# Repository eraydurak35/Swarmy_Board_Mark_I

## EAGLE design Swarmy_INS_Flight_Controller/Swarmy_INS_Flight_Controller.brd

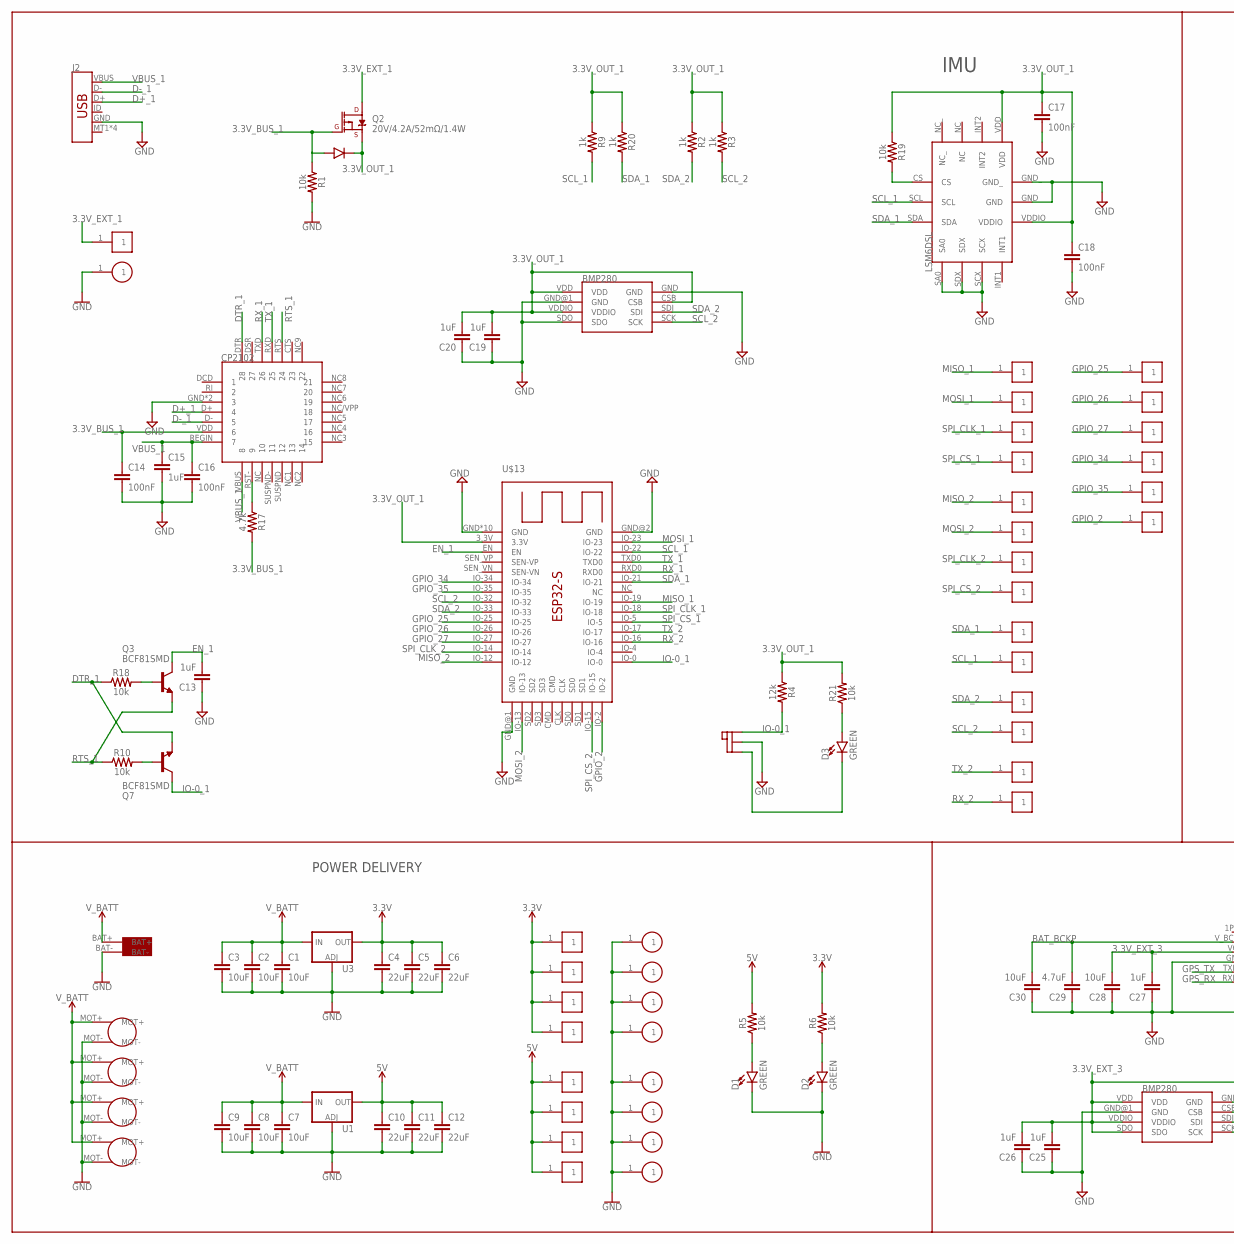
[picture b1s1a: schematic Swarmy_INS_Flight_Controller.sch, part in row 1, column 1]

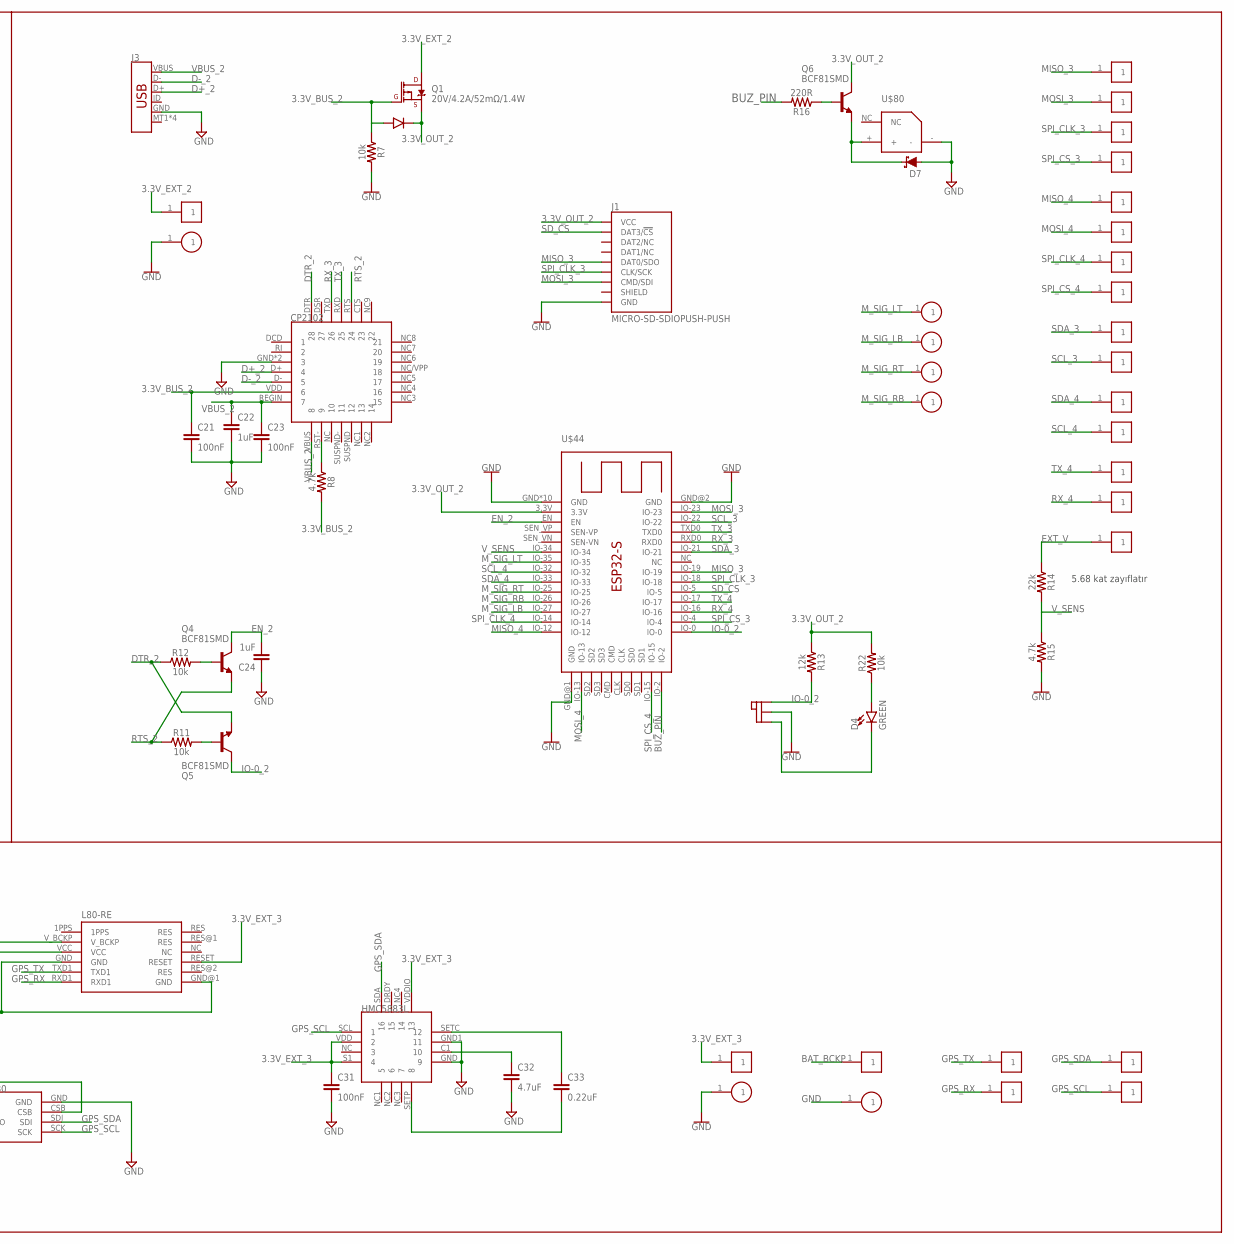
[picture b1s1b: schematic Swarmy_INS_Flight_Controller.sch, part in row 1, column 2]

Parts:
C1, C2, C3, C7, C8, C9, C28, C30: 10uF; 0603
C4, C5, C6, C10, C11, C12: 22uF; 0603
C13, C15, C19, C20, C22, C24, C25, C26, C27: 1uF; 0603
C14, C16, C17, C18, C21, C23, C31: 100nF; 0603
C29, C32: 4.7uF; 0603
C33: 0.22uF; 0603
D1, D2, D3, D4: GREEN; LED-0603
D7: 120mA/40V/370mV; SOD-523
J1: MICRO-SD-SDIOPUSH-PUSH; MICRO-SD-SOCKET
J2, J3: USB_MICRO-B_SMT; USB-MICROB
Q1, Q2: 20V/4.2A/52mΩ/1.4W; SOT23-3
Q3, Q4, Q5, Q6, Q7: BCF81SMD; SOT23-BEC
R1, R5, R6, R7, R10, R11, R12, R18, R19, R21, R22: 10k; 0603
R2, R3, R9, R20: 1k; 0603
R4, R13: 12k; 0603
R8, R15, R17: 4.7k; 0603
R14: 22k; 0603
R16: 220R; 0603
U1, U3: V_REG_LM1117SOT223; SOT223
U$1: 6X5MM_BATTERY_SOLDER_PADS
U$2, U$3, U$4, U$5: 3X4.5MM_MOTOR_SOLDER_PADS
U$6, U$7, U$8, U$9, U$10, U$11, U$12, U$22, U$23, U$29, U$30, U$31, U$32, U$33, U$34, U$35, U$36, U$37, U$38, U$39, U$40, U$41, U$42, U$45, U$50, U$51, U$52, U$53, U$54, U$55, U$56, U$57, U$58, U$59, U$60, U$61, U$62, U$63, U$65, U$67, U$69, U$71, U$72, U$73, U$74, U$81, U$82, U$83, U$84, U$85, U$86: 2X2MM_SQUARE_PAD
U$13, U$44: ESP32-S
U$14, U$15, U$16, U$17, U$18, U$19, U$20, U$21, U$24, U$46, U$68, U$70: 2X2MM_PAD
U$25, U$47: SOD_123_DIODE; SOD_23_DIODE
U$26: LSM6DSL_6DOF
U$27, U$66: BMP280
U$28, U$48: CP2102_SERIAL_TTL
U$43, U$49: SMD_SLIDE_SWITCH
U$64: L80-RE-M37
U$75: HMC5883L
U$76, U$77, U$78, U$79: 2X2MM_ROUND_PAD
U$80: PASIVE_BUZZER_5MM_X_5MM_20MM

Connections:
3.3V: C4.1, C5.1, C6.1, R6.2, U3.2 (OUT), U3.4 (OUT), U$6.1, U$7.1, U$8.1, U$22.1
3.3V_BUS_1: C14.1, Q2.1 (G), R1.1, R17.2, U$25.A, U$28.VDD (6)
3.3V_BUS_2: C21.1, Q1.1 (G), R7.1, R8.2, U$47.A, U$48.VDD (6)
3.3V_EXT_1: Q2.3 (D), U$23.1
3.3V_EXT_2: Q1.3 (D), U$45.1
3.3V_EXT_3: C25.2, C26.2, C27.2, C28.2, C31.1, U$64.RESET, U$64.VCC, U$66.CSB, U$66.SDO, U$66.VDD, U$66.VDDIO, U$67.1, U$75.S1 (4), U$75.VDD (2), U$75.VDDIO (13)
3.3V_OUT_1: C17.1, C18.1, C19.2, C20.2, Q2.2 (S), R2.1, R3.1, R4.1, R9.1, R19.1, R20.1, R21.2, U$13.3.3V, U$25.K, U$26.VDD, U$26.VDDIO, U$27.CSB, U$27.VDD, U$27.VDDIO
3.3V_OUT_2: J1.VCC, Q1.2 (S), Q6.C, R13.1, R22.2, U$44.3.3V, U$47.K
5V: C10.1, C11.1, C12.1, R5.2, U1.2 (OUT), U1.4 (OUT), U$9.1, U$10.1, U$11.1, U$12.1
BAT_BCKP: C29.2, C30.2, U$64.V_BCKP, U$69.1
BUZ_PIN: R16.2, U$44.IO-2
D+_1: J2.D+, U$28.D+ (4)
D+_2: J3.D+, U$48.D+ (4)
D-_1: J2.D-, U$28.D- (5)
D-_2: J3.D-, U$48.D- (5)
DTR_1: Q7.E, R18.1, U$28.DTR (28)
DTR_2: Q5.E, R12.1, U$48.DTR (28)
EN_1: C13.2, Q3.C, U$13.EN
EN_2: C24.2, Q4.C, U$44.EN
EXT_V: R14.1, U$65.1
GND: C1.2, C2.2, C3.2, C4.2, C5.2, C6.2, C7.2, C8.2, C9.2, C10.2, C11.2, C12.2, C13.1, C14.2, C15.2, C16.2, C17.2, C18.2, C19.1, C20.1, C21.2, C22.2, C23.2, C24.1, C25.1, C26.1, C27.1, C28.1, C29.1, C30.1, C31.2, C32.2, D1.C, D2.C, D7.A, J1.GND, J1.GND1 (GND), J1.GND3 (GND), J2.GND, J3.GND, R1.2, R7.2, R15.2, U1.1 (ADJ), U3.1 (ADJ), U$1.BAT-, U$2.MOT-, U$3.MOT-, U$4.MOT-, U$5.MOT-, U$13.GND, U$13.GND@1 (GND), U$13.GND@2 (GND), U$13.GND@3 (GND), U$13.GND@4 (GND), U$13.GND@5 (GND), U$13.GND@6 (GND), U$13.GND@7 (GND), U$13.GND@8 (GND), U$13.GND@9 (GND), U$13.GND@10 (GND), U$13.GND@11 (GND), U$14.1, U$15.1, U$16.1, U$17.1, U$18.1, U$19.1, U$20.1, U$21.1, U$24.1, U$26.GND, U$26.GND_, U$26.SA0, U$26.SCX, U$26.SDX, U$27.GND, U$27.GND@1 (GND), U$27.SDO, U$28.GND (3), U$28.GND1 (3), U$43.2, U$44.GND, U$44.GND@1 (GND), U$44.GND@2 (GND), U$44.GND@3 (GND), U$44.GND@4 (GND), U$44.GND@5 (GND), U$44.GND@6 (GND), U$44.GND@7 (GND), U$44.GND@8 (GND), U$44.GND@9 (GND), U$44.GND@10 (GND), U$44.GND@11 (GND), U$46.1, U$48.GND (3), U$48.GND1 (3), U$49.2, U$64.GND, U$64.GND@1 (GND), U$66.GND, U$66.GND@1 (GND), U$68.1, U$70.1, U$75.GND (9), U$75.GND1 (11), U$80.-
GPIO_2: U$13.IO-2, U$86.1
GPIO_25: U$13.IO-25, U$81.1
GPIO_26: U$13.IO-26, U$82.1
GPIO_27: U$13.IO-27, U$83.1
GPIO_34: U$13.IO-34, U$84.1
GPIO_35: U$13.IO-35, U$85.1
GPS_RX: U$64.RXD1, U$72.1
GPS_SCL: U$66.SCK, U$74.1, U$75.SCL (1)
GPS_SDA: U$66.SDI, U$73.1, U$75.SDA (16)
GPS_TX: U$64.TXD1, U$71.1
IO-0_1: Q7.C, R4.2, U$13.IO-0, U$43.3
IO-0_2: Q5.C, R13.2, U$44.IO-0, U$49.3
MISO_1: U$13.IO-19, U$29.1
MISO_2: U$13.IO-12, U$33.1
MISO_3: J1.DO/DAT0 (DAT0/SDO), U$44.IO-19, U$50.1
MISO_4: U$44.IO-12, U$54.1
MOSI_1: U$13.IO-23, U$30.1
MOSI_2: U$13.IO-13, U$34.1
MOSI_3: J1.DI/CMD (CMD/SDI), U$44.IO-23, U$51.1
MOSI_4: U$44.IO-13, U$55.1
M_SIG_LB: U$44.IO-27, U$77.1
M_SIG_LT: U$44.IO-35, U$76.1
M_SIG_RB: U$44.IO-26, U$79.1
M_SIG_RT: U$44.IO-25, U$78.1
unnamed: D1.A, R5.1
unnamed: D2.A, R6.1
unnamed: R8.1, U$48.RST- (9)
unnamed: Q5.B, R11.2
unnamed: Q4.B, R12.2
unnamed: D3.A, R21.1
unnamed: D4.A, R22.1
unnamed: D3.C, U$43.1
unnamed: D4.C, U$49.1
unnamed: Q6.B, R16.1
unnamed: R17.1, U$28.RST- (9)
unnamed: D7.C, Q6.E, U$80.+
unnamed: Q3.B, R18.2
unnamed: R19.2, U$26.CS
unnamed: Q7.B, R10.2
unnamed: C33.2, U$75.SETP (8)
unnamed: C32.1, U$75.C1 (10)
unnamed: C33.1, U$75.SETC (12)
RTS_1: Q3.E, R10.1, U$28.RTS (24)
RTS_2: Q4.E, R11.1, U$48.RTS (24)
RX_1: U$13.RXD0, U$28.TXD (26)
RX_2: U$13.IO-16, U$42.1
RX_3: U$44.RXD0, U$48.TXD (26)
RX_4: U$44.IO-16, U$63.1
SCL_1: R9.2, U$13.IO-22, U$26.SCL, U$38.1
SCL_2: R3.2, U$13.IO-32, U$27.SCK, U$40.1
SCL_3: U$44.IO-22, U$59.1
SCL_4: U$44.IO-32, U$61.1
SDA_1: R20.2, U$13.IO-21, U$26.SDA, U$37.1
SDA_2: R2.2, U$13.IO-33, U$27.SDI, U$39.1
SDA_3: U$44.IO-21, U$58.1
SDA_4: U$44.IO-33, U$60.1
SD_CS: J1.CS/DAT3 (DAT3/!CS!), U$44.IO-5
SPI_CLK_1: U$13.IO-18, U$31.1
SPI_CLK_2: U$13.IO-14, U$35.1
SPI_CLK_3: J1.SCLK (CLK/SCK), U$44.IO-18, U$52.1
SPI_CLK_4: U$44.IO-14, U$56.1
SPI_CS_1: U$13.IO-5, U$32.1
SPI_CS_2: U$13.IO-15, U$36.1
SPI_CS_3: U$44.IO-4, U$53.1
SPI_CS_4: U$44.IO-15, U$57.1
TX_1: U$13.TXD0, U$28.RXD (25)
TX_2: U$13.IO-17, U$41.1
TX_3: U$44.TXD0, U$48.RXD (25)
TX_4: U$44.IO-17, U$62.1
VBUS_1: C15.1, C16.1, J2.VBUS, U$28.REGIN (7), U$28.VBUS (8)
VBUS_2: C22.1, C23.1, J3.VBUS, U$48.REGIN (7), U$48.VBUS (8)
V_BATT: C1.1, C2.1, C3.1, C7.1, C8.1, C9.1, U1.3 (IN), U3.3 (IN), U$1.BAT+, U$2.MOT+, U$3.MOT+, U$4.MOT+, U$5.MOT+
V_SENS: R14.2, R15.1, U$44.IO-34

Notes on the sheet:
POWER DELIVERY
IMU
5.68 kat zayıflatır

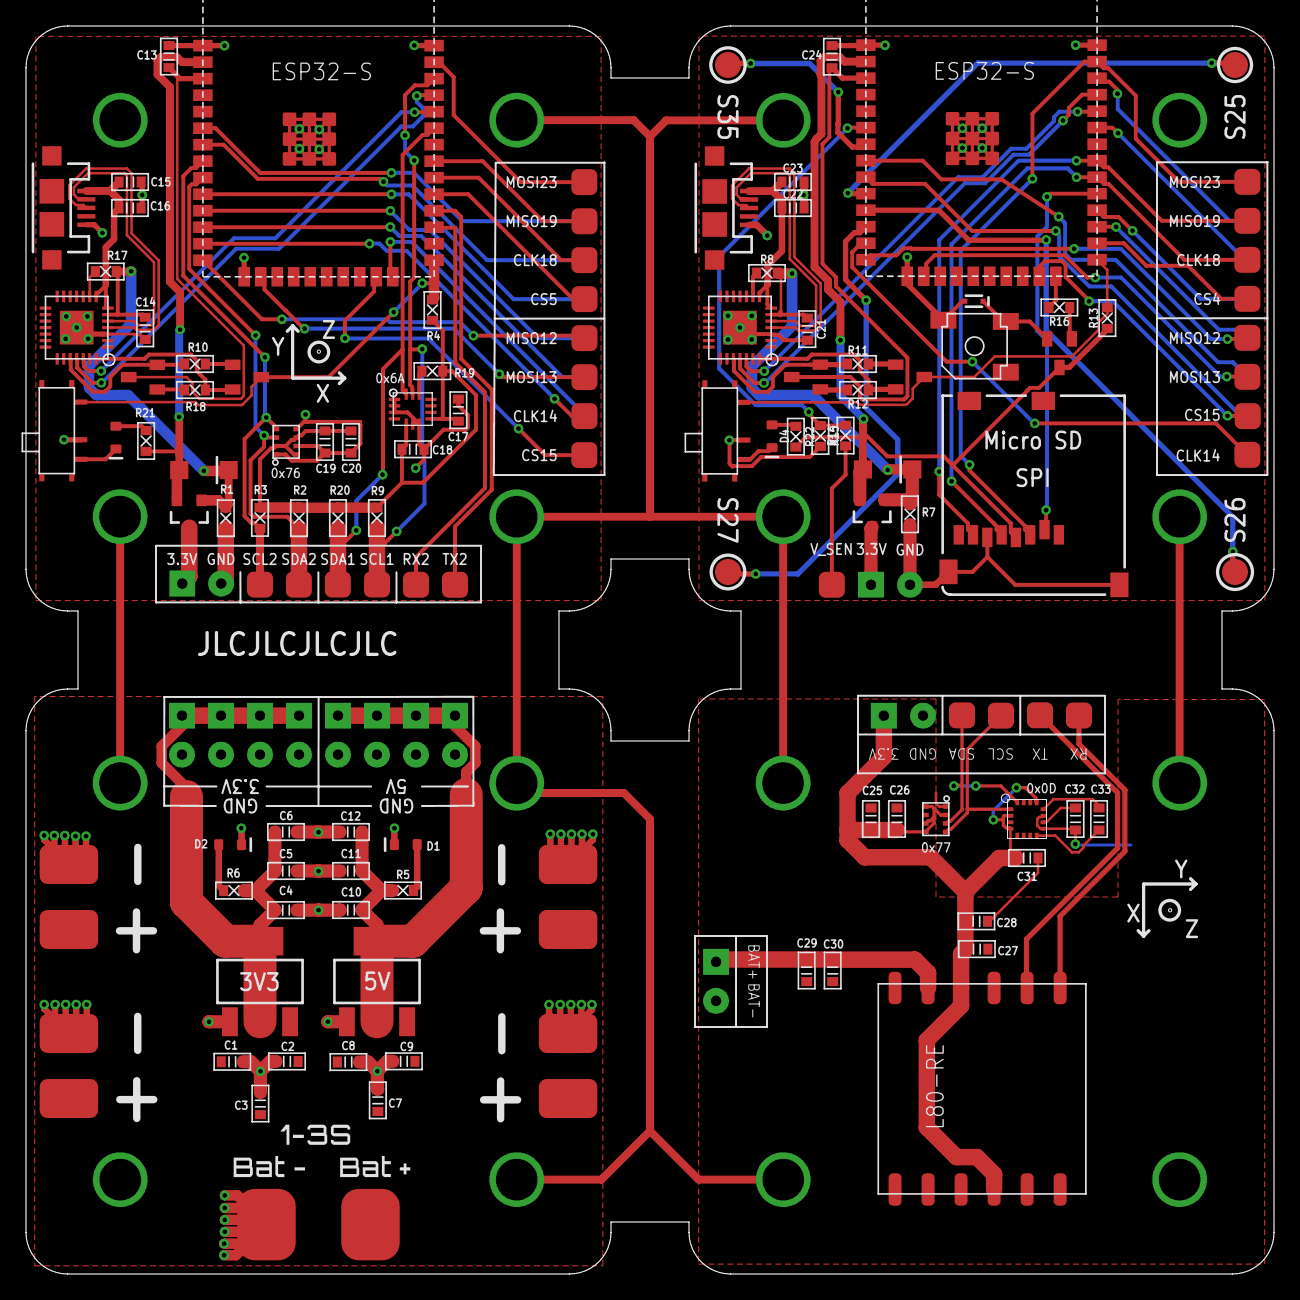
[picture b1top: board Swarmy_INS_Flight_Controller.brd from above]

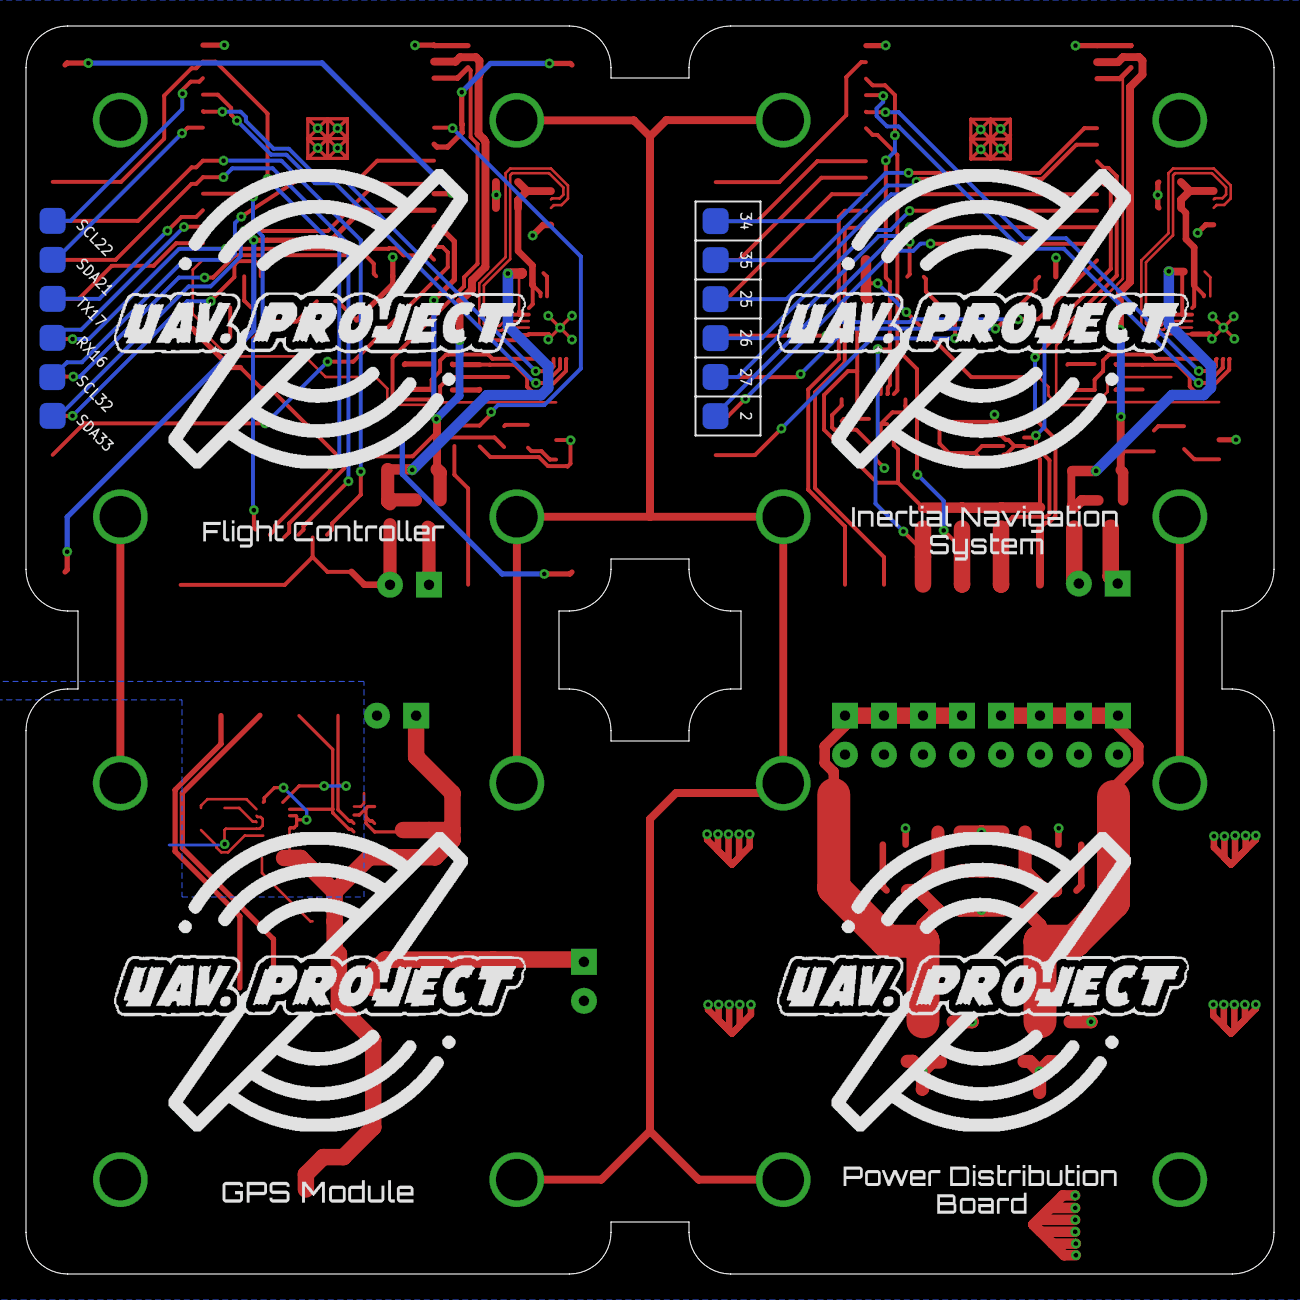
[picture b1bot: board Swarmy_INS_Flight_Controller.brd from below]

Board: 2 copper layers, 96.0 x 96.0 mm, 158 parts (13 on the bottom side), 94 nets.

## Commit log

2022-05-10 Final Form

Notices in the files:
parts and their libraries:
SparkFun-Capacitors: Licensing: Creative Commons ShareAlike 4.0 International - https://creativecommons.org/licenses/by-sa/4.0
